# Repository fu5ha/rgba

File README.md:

# `rgba` - reasonably good bluetooth audio

The `rgba` is a tiny (41x20mm PCB), extremely high fidelity Bluetooth audio receiver meant to attach inline to the cord of
a pair of IEMs. It aims to provide as high quality audio as possible while retaining reasonable battery life and
its small form factor. It is designed to pair well with high sensitivity, low impedance IEMs. For use with
lower sensitivity, harder to drive headphones (or IEMs), you'll need to adjust the values of the resistor feedback network
around the Op Amp to provide the proper output power. See [this document](https://www.ti.com/lit/ug/tiduaw1/tiduaw1.pdf),
especially sections 1 through 3, for more information. Reach out to me via GitHub issue or social media (listed on my
GitHub profile) and I'd be happy to guide you on this.

## Schematic

See [rgba.pdf](/rgba.pdf) for a PDF copy of the schematic, or open the repo's root as a project in KiCad and launch Eeschema.

## Renders

Here are a couple of renders of the latest version of the PCB.

## Bill of Materials

A bill of materials is available in HTML format, with links to sourcing information and
interactive PCB board view useful when performing assembly. View it here: <https://termhn.github.io/rgba/ibom.html>

Not included in the BOM is a battery. You can use any single cell LiPo (3.7V) LiPo battery up to
500mAh in capacity. You'll likely need to either re-terminate the batteries with the proper connector
(2-pin JST-ACH [plug housing](https://www.digikey.com/en/products/detail/jst-sales-america-inc/ACHR-02V-S/1647783c)
and [crimp leads](https://www.digikey.com/en/products/detail/jst-sales-america-inc/ASACHSACH28W51/6009445)
can be found on DigiKey) or lop off the included connector and solder the leads directly to the board.

## PCB Sourcing

I recommend ordering PCBs through OSH Park because their 4 layer process has the needed precision at a reasonable price
(JLCPCB for example will cost you a lot more to get the needed 0.2/0.4 diameter vias), is good quality, and are a cool
organization to support. Plus their PCBs are a super purdy purple :d

You can order some of the rev 1.1 PCBs directly using this link: -link will be inserted here when it has been tested working-

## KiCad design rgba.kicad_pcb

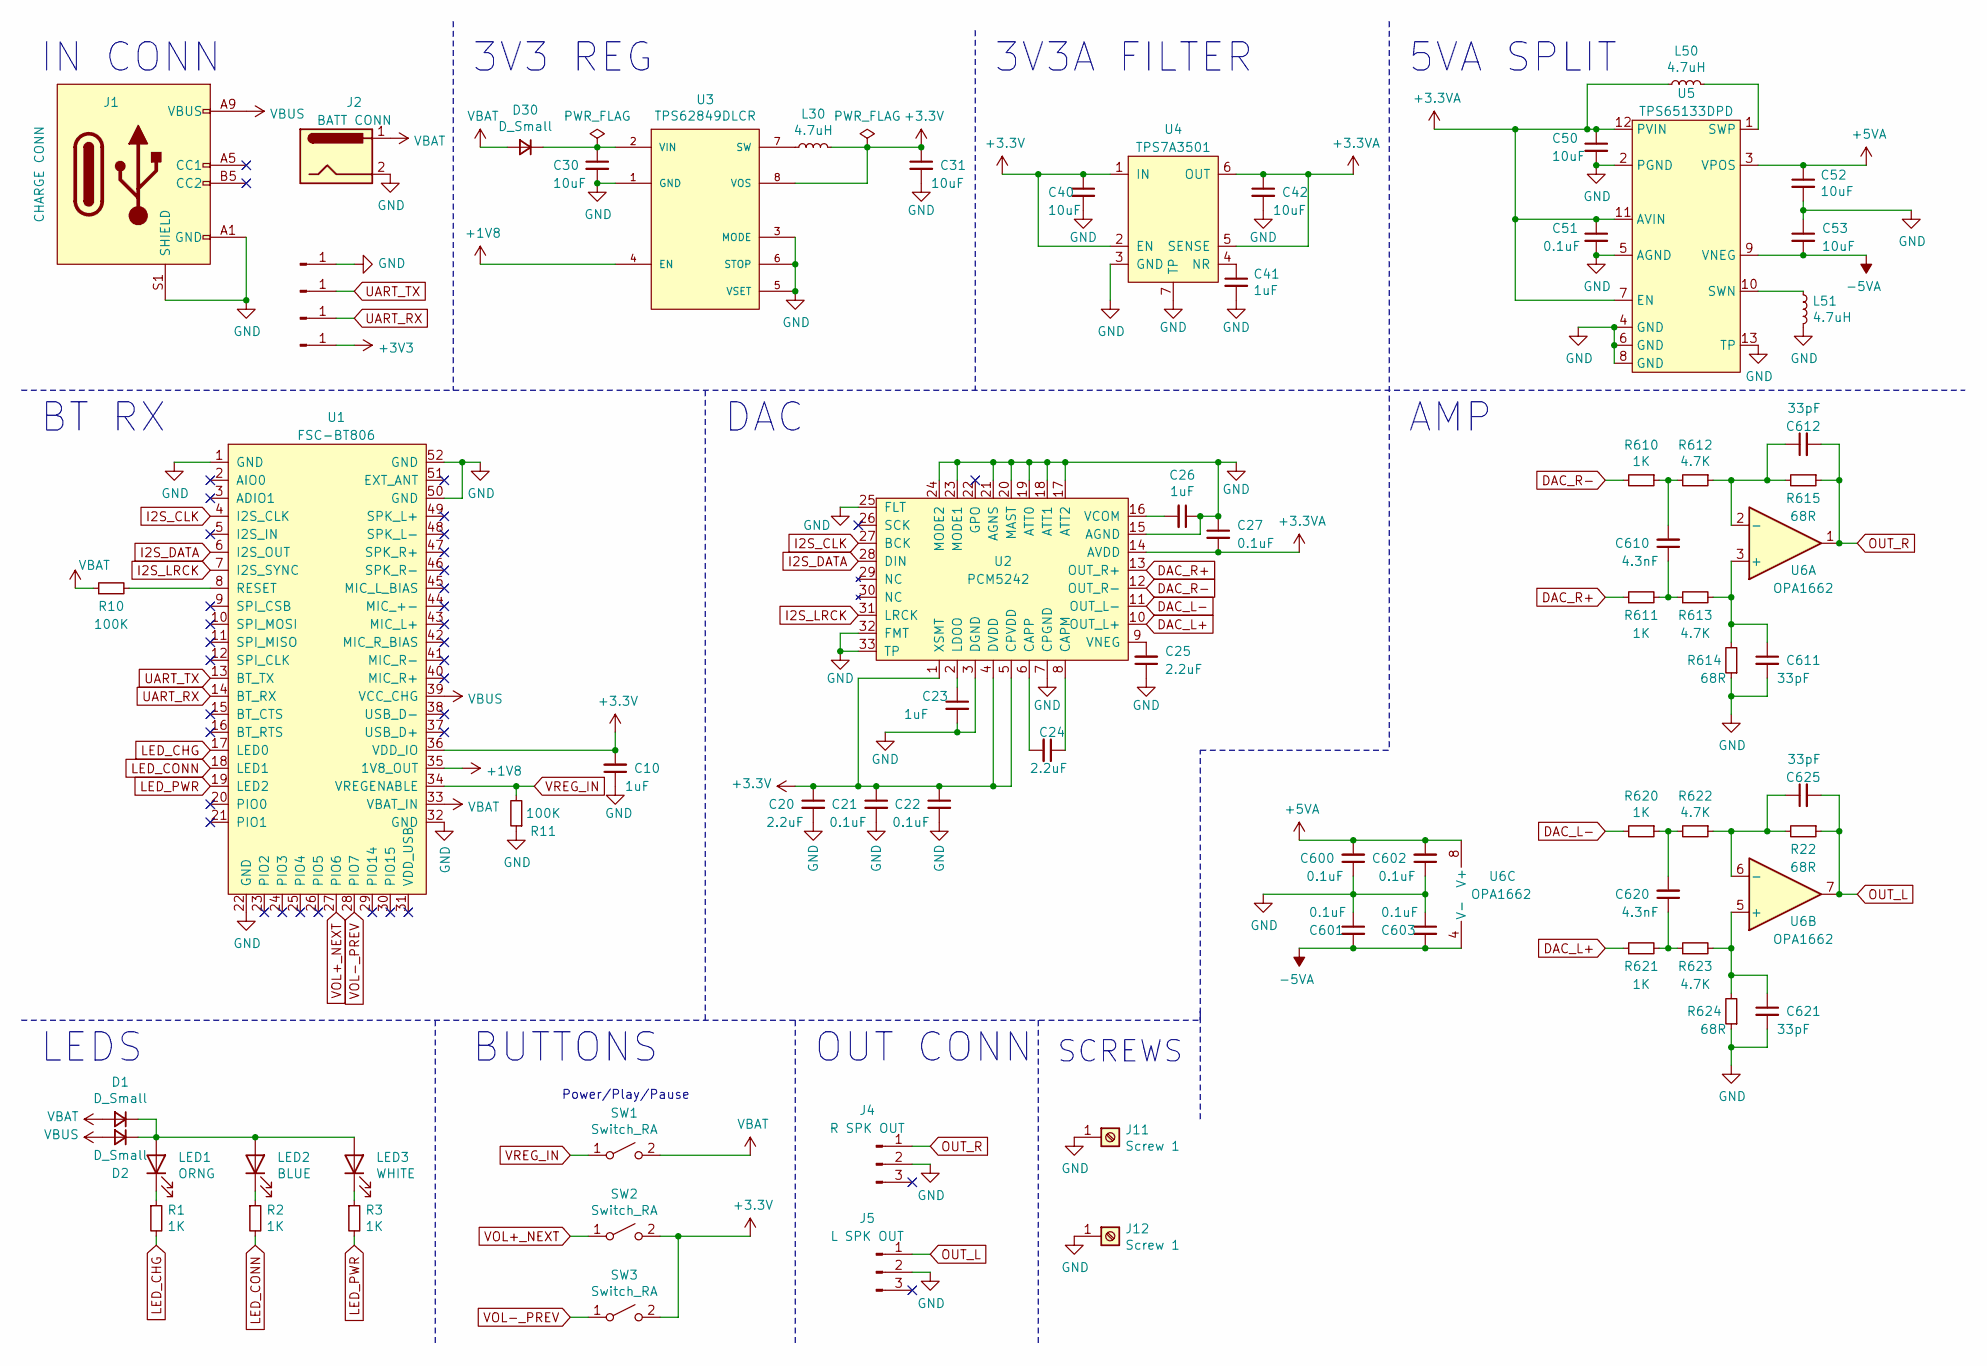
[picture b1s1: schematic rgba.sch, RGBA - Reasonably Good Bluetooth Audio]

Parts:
C10, C23, C26, C41: 1uF; C_0402_1005Metric_Pad0.74x0.62mm_HandSolder
C20, C24, C25: 2.2uF; C_0805_2012Metric_Pad1.18x1.45mm_HandSolder
C21, C22, C27, C51, C600, C601, C602, C603: 0.1uF; C_0402_1005Metric_Pad0.74x0.62mm_HandSolder
C30, C31, C40, C42, C50, C52, C53: 10uF; C_0402_1005Metric_Pad0.74x0.62mm_HandSolder
C610, C620: 4.3nF; C_0603_1608Metric_Pad1.08x0.95mm_HandSolder
C611, C612, C621, C625: 33pF; C_0603_1608Metric_Pad1.08x0.95mm_HandSolder
D1, D2, D30: D_Small; D_0603_1608Metric_Pad1.05x0.95mm_HandSolder
J1: CHARGE CONN; USB_C_Receptacle_UJC-HP-3-SMT-TR
J2: BATT CONN; JST_ACH_BM02B-ACHSS-GAN-ETF_1x02-1MP_P1.20mm_Vertical
J3: UART_GND; TestPoint_THTPad_D1.5mm_Drill0.7mm
J4: R SPK OUT; SolderWire_AudioOut_1x03_P2.0mm
J5: L SPK OUT; SolderWire_AudioOut_1x03_P2.0mm
J6: UART_TX; TestPoint_THTPad_D1.5mm_Drill0.7mm
J7: UART_VBUS; TestPoint_THTPad_D1.5mm_Drill0.7mm
J8: UART_RX; TestPoint_THTPad_D1.5mm_Drill0.7mm
J11, J12: Screw 1; MountingHole_1.2mm_M1_Pad
L30, L50, L51: 4.7uH; L_1008_2520Metric_Pad1.43x2.20mm_HandSolder
LED1: ORNG; LED_0603_1608Metric_Castellated
LED2: BLUE; LED_0603_1608Metric_Castellated
LED3: WHITE; LED_0603_1608Metric_Castellated
R1, R2, R3, R610, R611, R620, R621: 1K; R_0603_1608Metric_Pad0.98x0.95mm_HandSolder
R10, R11: 100K; R_0402_1005Metric_Pad0.72x0.64mm_HandSolder
R22, R614, R615, R624: 68R; R_0402_1005Metric_Pad0.72x0.64mm_HandSolder
R612, R613, R622, R623: 4.7K; R_0402_1005Metric_Pad0.72x0.64mm_HandSolder
SW1, SW2, SW3: Switch_RA; TL4110AF160Q
U1: FSC-BT806
U2: PCM5242; QFN-32-1EP_5x5mm_P0.5mm_EP3.45x3.45mm
U3: TPS62849DLCR; VSON-8_1.5x2mm_P0.5mm
U4: TPS7A3501; WSON-6-1EP_2x2mm_P0.65mm_EP1x1.6mm_ThermalVias
U5: TPS65133DPD; WSON-12-1EP_3x3mm_P0.45mm_EP1.2x2mm
U6: OPA1662; VSSOP-8_3.0x3.0mm_P0.65mm

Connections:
+1V8: U1.35 (1V8_OUT), U3.4 (EN)
+3.3VA: C27.2, C42.1, C50.1, C51.1, L50.1, U2.14 (AVDD), U4.5 (SENSE), U4.6 (OUT), U5.7 (EN), U5.11 (AVIN), U5.12 (PVIN)
+5VA: C52.1, C600.2, C602.2, U5.3 (VPOS), U6.8 (V+)
-5VA: C53.2, C601.2, C603.2, U5.9 (VNEG), U6.4 (V-)
DAC_L+: R621.1, U2.10 (OUT_L+)
DAC_L-: R620.2, U2.11 (OUT_L-)
DAC_R+: R611.1, U2.13 (OUT_R+)
DAC_R-: R610.2, U2.12 (OUT_R-)
GND: C10.1, C20.2, C21.2, C22.2, C23.2, C25.1, C26.1, C27.1, C30.2, C31.2, C40.2, C41.2, C42.2, C50.2, C51.2, C52.2, C53.1, C600.1, C601.1, C602.1, C603.1, C611.2, C621.2, J1.A1 (GND), J1.B1 (GND), J1.S1 (SHIELD), J2.2, J3.1, J4.2, J5.2, J11.1, J12.1, L51.2, R11.1, R614.1, R624.1, U1.1 (GND), U1.22 (GND), U1.32 (GND), U1.50 (GND), U1.52 (GND), U2.3 (DGND), U2.7 (CPGND), U2.15 (AGND), U2.17 (ATT2), U2.18 (ATT1), U2.19 (ATT0), U2.20 (MAST), U2.21 (AGNS), U2.23 (MODE1), U2.24 (MODE2), U2.25 (FLT), U2.32 (FMT), U2.33 (TP), U3.1 (GND), U3.3 (MODE), U3.5 (VSET), U3.6 (STOP), U4.3 (GND), U4.7 (TP), U5.2 (PGND), U5.4 (GND), U5.5 (AGND), U5.6 (GND), U5.8 (GND), U5.13 (TP)
I2S_CLK: U1.4 (I2S_CLK), U2.27 (BCK)
I2S_DATA: U1.6 (I2S_OUT), U2.28 (DIN)
I2S_LRCK: U1.7 (I2S_SYNC), U2.31 (LRCK)
LED_CHG: R1.2, U1.17 (LED0)
LED_CONN: R2.2, U1.18 (LED1)
LED_PWR: R3.2, U1.19 (LED2)
unnamed: C23.1, U2.2 (LDOO)
unnamed: C24.1, U2.8 (CAPM)
unnamed: C24.2, U2.6 (CAPP)
unnamed: C25.2, U2.9 (VNEG)
unnamed: C26.2, U2.16 (VCOM)
unnamed: C30.1, D30.1 (K), U3.2 (VIN)
unnamed: C41.1, U4.4 (NR)
unnamed: C610.1, R611.2, R613.1
unnamed: C610.2, R610.1, R612.2
unnamed: C611.1, R613.2, R614.2, U6.3 (+)
unnamed: C612.1, R612.1, R615.2, U6.2 (-)
unnamed: C620.1, R621.2, R623.1
unnamed: C620.2, R620.1, R622.2
unnamed: C621.1, R623.2, R624.2, U6.5 (+)
unnamed: C625.1, R22.2, R622.1, U6.6 (-)
unnamed: D1.1 (K), D2.1 (K), LED1.2 (A), LED2.2 (A), LED3.2 (A)
unnamed: L30.1, U3.7 (SW)
unnamed: L50.2, U5.1 (SWP)
unnamed: L51.1, U5.10 (SWN)
unnamed: LED1.1 (K), R1.1
unnamed: LED2.1 (K), R2.1
unnamed: LED3.1 (K), R3.1
unnamed: R10.2, U1.8 (RESET)
OUT_L: C625.2, J5.1, R22.1, U6.7
OUT_R: C612.2, J4.1, R615.1, U6.1
UART_RX: J8.1, U1.14 (BT_RX)
UART_TX: J6.1, U1.13 (BT_TX)
VBAT: D1.2 (A), D30.2 (A), J2.1, R10.1, SW1.2 (B), U1.33 (VBAT_IN)
VBUS: D2.2 (A), J1.A9 (VBUS), J1.B9 (VBUS), U1.39 (VCC_CHG)
VOL+_NEXT: SW2.1 (A), U1.27 (PIO6)
VOL-_PREV: SW3.1 (A), U1.28 (PIO7)
VREG_IN: R11.2, SW1.1 (A), U1.34 (VREGENABLE)

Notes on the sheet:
DAC
BT RX
IN CONN
3V3 REG
3V3A FILTER
AMP
LEDS
BUTTONS
OUT CONN
5VA SPLIT
SCREWS
Power/Play/Pause

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
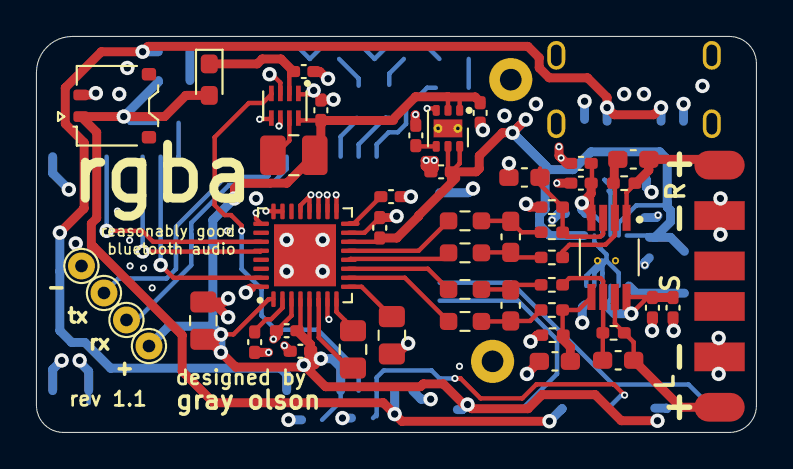
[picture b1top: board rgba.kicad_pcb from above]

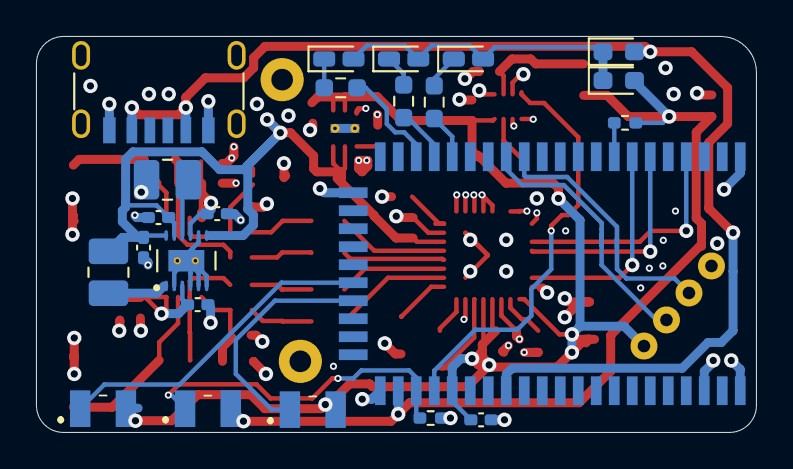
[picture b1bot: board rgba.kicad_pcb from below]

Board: 4 copper layers, 40.0 x 22.0 mm, 73 parts (23 on the bottom side), 48 nets.

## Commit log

2021-03-07 fix link in readme
2021-03-07 add license
2021-03-13 new 3.3v voltage regulator and updated a few footprints
2021-03-30 start working on new regulator
2021-03-31 rev 1.1
2021-03-31 update readme, gerbers, bom
2021-03-31 github pages
2021-03-31 funding
2021-03-31 gitignore, fix funding
2021-03-31 Set theme jekyll-theme-minimal
2021-03-31 add ibom to readme
2021-04-01 modify uart header and led position
2021-04-01 readme change
2021-04-01 more size optimization
2021-04-01 make UART terminals larger
2021-04-04 connect programming header power to 3v3 instead of vbus
2021-04-04 remove TPS62849 enable pin pulldown resistor because it has an internal pulldown resistor
